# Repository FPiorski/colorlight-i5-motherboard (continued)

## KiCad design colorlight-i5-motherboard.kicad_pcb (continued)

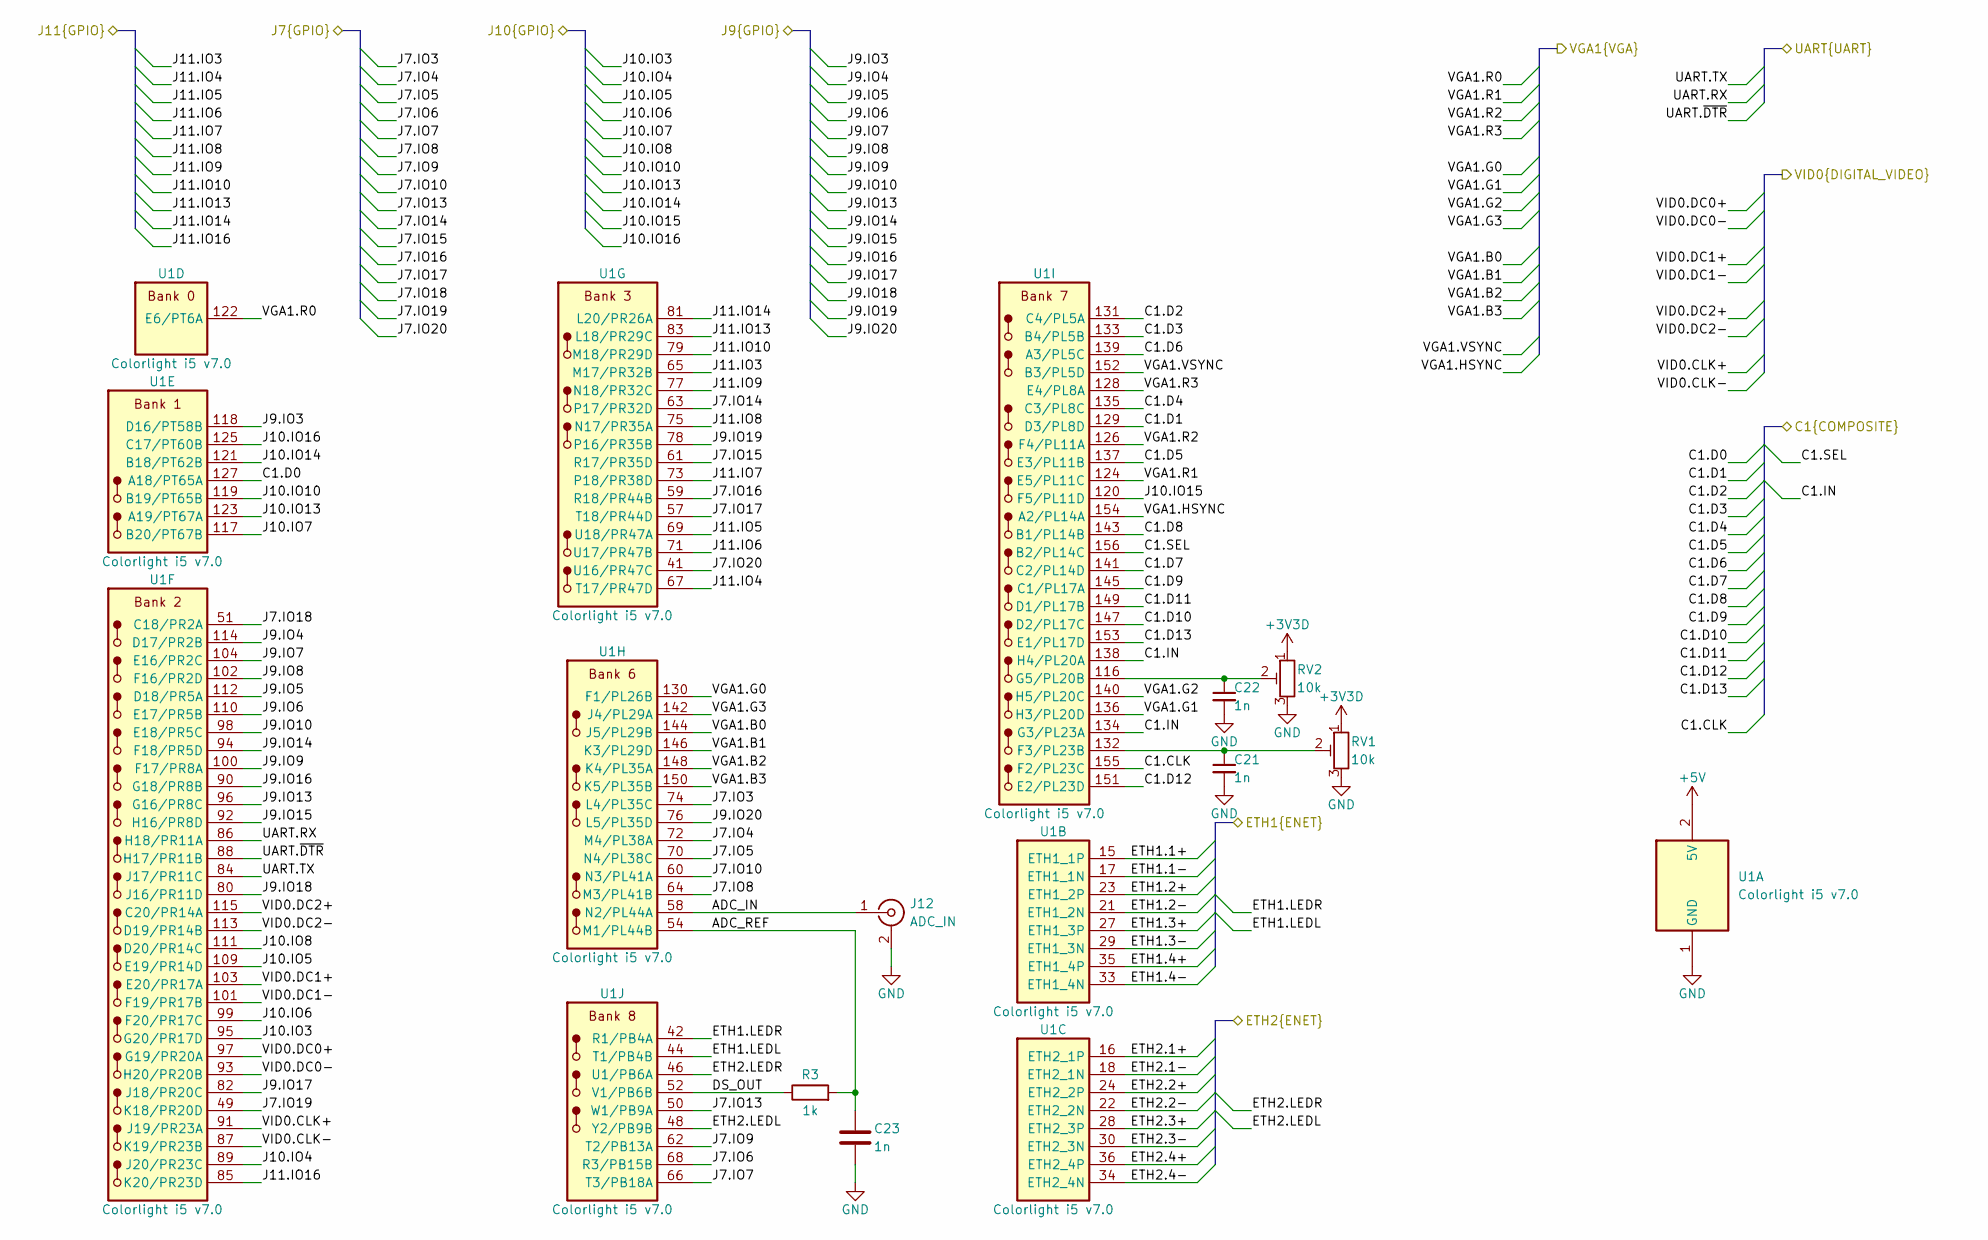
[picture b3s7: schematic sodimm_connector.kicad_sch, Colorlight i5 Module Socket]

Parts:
C21, C22, C23: 1n; C_0402_1005Metric
J12: ADC_IN; U.FL_Hirose_U.FL-R-SMT-1_Vertical; LCSC C5137195
R3: 1k; R_0402_1005Metric
RV1, RV2: 10k; Potentiometer_Bourns_TC33X_Vertical; LCSC C719176
U1: Colorlight i5 v7.0; JST_DM-7D4-H2500_2x100_P0.6mm_Polarized_Socket_Horizontal

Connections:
+3V3D: RV1.1, RV2.1; also elsewhere on the board
+5V: U1.2 (5V), U1.4 (5V), U1.6 (5V), U1.8 (5V), U1.10 (5V), U1.12 (5V); also elsewhere on the board
/Analog Video/C1.CLK: U1.155 (F2/PL23C); also elsewhere on the board
/Analog Video/C1.D0: U1.127 (A18/PT65A); also elsewhere on the board
/Analog Video/C1.D1: U1.129 (D3/PL8D); also elsewhere on the board
/Analog Video/C1.D2: U1.131 (C4/PL5A); also elsewhere on the board
/Analog Video/C1.D3: U1.133 (B4/PL5B); also elsewhere on the board
/Analog Video/C1.D4: U1.135 (C3/PL8C); also elsewhere on the board
/Analog Video/C1.D5: U1.137 (E3/PL11B); also elsewhere on the board
/Analog Video/C1.D6: U1.139 (A3/PL5C); also elsewhere on the board
/Analog Video/C1.D7: U1.141 (C2/PL14D); also elsewhere on the board
/Analog Video/C1.D8: U1.143 (B1/PL14B); also elsewhere on the board
/Analog Video/C1.D9: U1.145 (C1/PL17A); also elsewhere on the board
/Analog Video/C1.D10: U1.147 (D2/PL17C); also elsewhere on the board
/Analog Video/C1.D11: U1.149 (D1/PL17B); also elsewhere on the board
/Analog Video/C1.D12: U1.151 (E2/PL23D); also elsewhere on the board
/Analog Video/C1.D13: U1.153 (E1/PL17D); also elsewhere on the board
/Analog Video/C1.IN: U1.134 (G3/PL23A), U1.138 (H4/PL20A); also elsewhere on the board
/Analog Video/C1.SEL: U1.156 (B2/PL14C); also elsewhere on the board
/Analog Video/VGA1.B0: U1.144 (J5/PL29B); also elsewhere on the board
/Analog Video/VGA1.B1: U1.146 (K3/PL29D); also elsewhere on the board
/Analog Video/VGA1.B2: U1.148 (K4/PL35A); also elsewhere on the board
/Analog Video/VGA1.B3: U1.150 (K5/PL35B); also elsewhere on the board
/Analog Video/VGA1.G0: U1.130 (F1/PL26B); also elsewhere on the board
/Analog Video/VGA1.G1: U1.136 (H3/PL20D); also elsewhere on the board
/Analog Video/VGA1.G2: U1.140 (H5/PL20C); also elsewhere on the board
/Analog Video/VGA1.G3: U1.142 (J4/PL29A); also elsewhere on the board
/Analog Video/VGA1.HSYNC: U1.154 (A2/PL14A); also elsewhere on the board
/Analog Video/VGA1.R0: U1.122 (E6/PT6A); also elsewhere on the board
/Analog Video/VGA1.R1: U1.124 (E5/PL11C); also elsewhere on the board
/Analog Video/VGA1.R2: U1.126 (F4/PL11A); also elsewhere on the board
/Analog Video/VGA1.R3: U1.128 (E4/PL8A); also elsewhere on the board
/Analog Video/VGA1.VSYNC: U1.152 (B3/PL5D); also elsewhere on the board
/Digital Video/VID0.CLK+: U1.91 (J19/PR23A); also elsewhere on the board
/Digital Video/VID0.CLK-: U1.87 (K19/PR23B); also elsewhere on the board
/Digital Video/VID0.DC0+: U1.97 (G19/PR20A); also elsewhere on the board
/Digital Video/VID0.DC0-: U1.93 (H20/PR20B); also elsewhere on the board
/Digital Video/VID0.DC1+: U1.103 (E20/PR17A); also elsewhere on the board
/Digital Video/VID0.DC1-: U1.101 (F19/PR17B); also elsewhere on the board
/Digital Video/VID0.DC2+: U1.115 (C20/PR14A); also elsewhere on the board
/Digital Video/VID0.DC2-: U1.113 (D19/PR14B); also elsewhere on the board
/Ethernet/ETH1.1+: U1.15 (ETH1_1P); also elsewhere on the board
/Ethernet/ETH1.1-: U1.17 (ETH1_1N); also elsewhere on the board
/Ethernet/ETH1.2+: U1.23 (ETH1_2P); also elsewhere on the board
/Ethernet/ETH1.2-: U1.21 (ETH1_2N); also elsewhere on the board
/Ethernet/ETH1.3+: U1.27 (ETH1_3P); also elsewhere on the board
/Ethernet/ETH1.3-: U1.29 (ETH1_3N); also elsewhere on the board
/Ethernet/ETH1.4+: U1.35 (ETH1_4P); also elsewhere on the board
/Ethernet/ETH1.4-: U1.33 (ETH1_4N); also elsewhere on the board
/Ethernet/ETH1.LEDL: U1.44 (T1/PB4B); also elsewhere on the board
/Ethernet/ETH1.LEDR: U1.42 (R1/PB4A); also elsewhere on the board
/Ethernet/ETH2.1+: U1.16 (ETH2_1P); also elsewhere on the board
/Ethernet/ETH2.1-: U1.18 (ETH2_1N); also elsewhere on the board
/Ethernet/ETH2.2+: U1.24 (ETH2_2P); also elsewhere on the board
/Ethernet/ETH2.2-: U1.22 (ETH2_2N); also elsewhere on the board
/Ethernet/ETH2.3+: U1.28 (ETH2_3P); also elsewhere on the board
/Ethernet/ETH2.3-: U1.30 (ETH2_3N); also elsewhere on the board
/Ethernet/ETH2.4+: U1.36 (ETH2_4P); also elsewhere on the board
/Ethernet/ETH2.4-: U1.34 (ETH2_4N); also elsewhere on the board
/Ethernet/ETH2.LEDL: U1.48 (Y2/PB9B); also elsewhere on the board
/Ethernet/ETH2.LEDR: U1.46 (U1/PB6A); also elsewhere on the board
/GPIO/J7.IO3: U1.74 (L4/PL35C); also elsewhere on the board
/GPIO/J7.IO4: U1.72 (M4/PL38A); also elsewhere on the board
/GPIO/J7.IO5: U1.70 (N4/PL38C); also elsewhere on the board
/GPIO/J7.IO6: U1.68 (R3/PB15B); also elsewhere on the board
/GPIO/J7.IO7: U1.66 (T3/PB18A); also elsewhere on the board
/GPIO/J7.IO8: U1.64 (M3/PL41B); also elsewhere on the board
/GPIO/J7.IO9: U1.62 (T2/PB13A); also elsewhere on the board
/GPIO/J7.IO10: U1.60 (N3/PL41A); also elsewhere on the board
/GPIO/J7.IO13: U1.50 (W1/PB9A); also elsewhere on the board
/GPIO/J7.IO14: U1.63 (P17/PR32D); also elsewhere on the board
/GPIO/J7.IO15: U1.61 (R17/PR35D); also elsewhere on the board
/GPIO/J7.IO16: U1.59 (R18/PR44B); also elsewhere on the board
/GPIO/J7.IO17: U1.57 (T18/PR44D); also elsewhere on the board
/GPIO/J7.IO18: U1.51 (C18/PR2A); also elsewhere on the board
/GPIO/J7.IO19: U1.49 (K18/PR20D); also elsewhere on the board
/GPIO/J7.IO20: U1.41 (U16/PR47C); also elsewhere on the board
/GPIO/J9.IO3: U1.118 (D16/PT58B); also elsewhere on the board
/GPIO/J9.IO4: U1.114 (D17/PR2B); also elsewhere on the board
/GPIO/J9.IO5: U1.112 (D18/PR5A); also elsewhere on the board
/GPIO/J9.IO6: U1.110 (E17/PR5B); also elsewhere on the board
/GPIO/J9.IO7: U1.104 (E16/PR2C); also elsewhere on the board
/GPIO/J9.IO8: U1.102 (F16/PR2D); also elsewhere on the board
/GPIO/J9.IO9: U1.100 (F17/PR8A); also elsewhere on the board
/GPIO/J9.IO10: U1.98 (E18/PR5C); also elsewhere on the board
/GPIO/J9.IO13: U1.96 (G16/PR8C); also elsewhere on the board
/GPIO/J9.IO14: U1.94 (F18/PR5D); also elsewhere on the board
/GPIO/J9.IO15: U1.92 (H16/PR8D); also elsewhere on the board
/GPIO/J9.IO16: U1.90 (G18/PR8B); also elsewhere on the board
/GPIO/J9.IO17: U1.82 (J18/PR20C); also elsewhere on the board
/GPIO/J9.IO18: U1.80 (J16/PR11D); also elsewhere on the board
/GPIO/J9.IO19: U1.78 (P16/PR35B); also elsewhere on the board
/GPIO/J9.IO20: U1.76 (L5/PL35D); also elsewhere on the board
/GPIO/J10.IO3: U1.95 (G20/PR17D); also elsewhere on the board
/GPIO/J10.IO4: U1.89 (J20/PR23C); also elsewhere on the board
/GPIO/J10.IO5: U1.109 (E19/PR14D); also elsewhere on the board
/GPIO/J10.IO6: U1.99 (F20/PR17C); also elsewhere on the board
/GPIO/J10.IO7: U1.117 (B20/PT67B); also elsewhere on the board
/GPIO/J10.IO8: U1.111 (D20/PR14C); also elsewhere on the board
/GPIO/J10.IO10: U1.119 (B19/PT65B); also elsewhere on the board
/GPIO/J10.IO13: U1.123 (A19/PT67A); also elsewhere on the board
/GPIO/J10.IO14: U1.121 (B18/PT62B); also elsewhere on the board
/GPIO/J10.IO15: U1.120 (F5/PL11D); also elsewhere on the board
/GPIO/J10.IO16: U1.125 (C17/PT60B); also elsewhere on the board
/GPIO/J11.IO3: U1.65 (M17/PR32B); also elsewhere on the board
/GPIO/J11.IO4: U1.67 (T17/PR47D); also elsewhere on the board
/GPIO/J11.IO5: U1.69 (U18/PR47A); also elsewhere on the board
/GPIO/J11.IO6: U1.71 (U17/PR47B); also elsewhere on the board
/GPIO/J11.IO7: U1.73 (P18/PR38D); also elsewhere on the board
/GPIO/J11.IO8: U1.75 (N17/PR35A); also elsewhere on the board
/GPIO/J11.IO9: U1.77 (N18/PR32C); also elsewhere on the board
/GPIO/J11.IO10: U1.79 (M18/PR29D); also elsewhere on the board
/GPIO/J11.IO13: U1.83 (L18/PR29C); also elsewhere on the board
/GPIO/J11.IO14: U1.81 (L20/PR26A); also elsewhere on the board
/GPIO/J11.IO16: U1.85 (K20/PR23D); also elsewhere on the board
/SODIMM Connector/ADC_IN: J12.1 (In), U1.58 (N2/PL44A)
/SODIMM Connector/ADC_REF: C23.1, R3.2, U1.54 (M1/PL44B)
/SODIMM Connector/DS_OUT: R3.1, U1.52 (V1/PB6B)
/SODIMM Connector/UART.RX: U1.86 (H18/PR11A); also elsewhere on the board
/SODIMM Connector/UART.TX: U1.84 (J17/PR11C); also elsewhere on the board
/SODIMM Connector/UART.~DTR: U1.88 (H17/PR11B); also elsewhere on the board
GND: C21.2, C22.2, C23.2, J12.2 (Ext), RV1.3, RV2.3, U1.1 (GND), U1.3 (GND), U1.5 (GND), U1.7 (GND), U1.9 (GND), U1.11 (GND), U1.39 (GND), U1.40 (GND), U1.55 (GND), U1.56 (GND), U1.105 (GND), U1.106 (GND), U1.107 (GND), U1.108 (GND), U1.157 (GND), U1.158 (GND), U1.199 (GND), U1.200 (GND); also elsewhere on the board
unnamed: C21.1, RV1.2, U1.132 (F3/PL23B)
unnamed: C22.1, RV2.2, U1.116 (G5/PL20B)

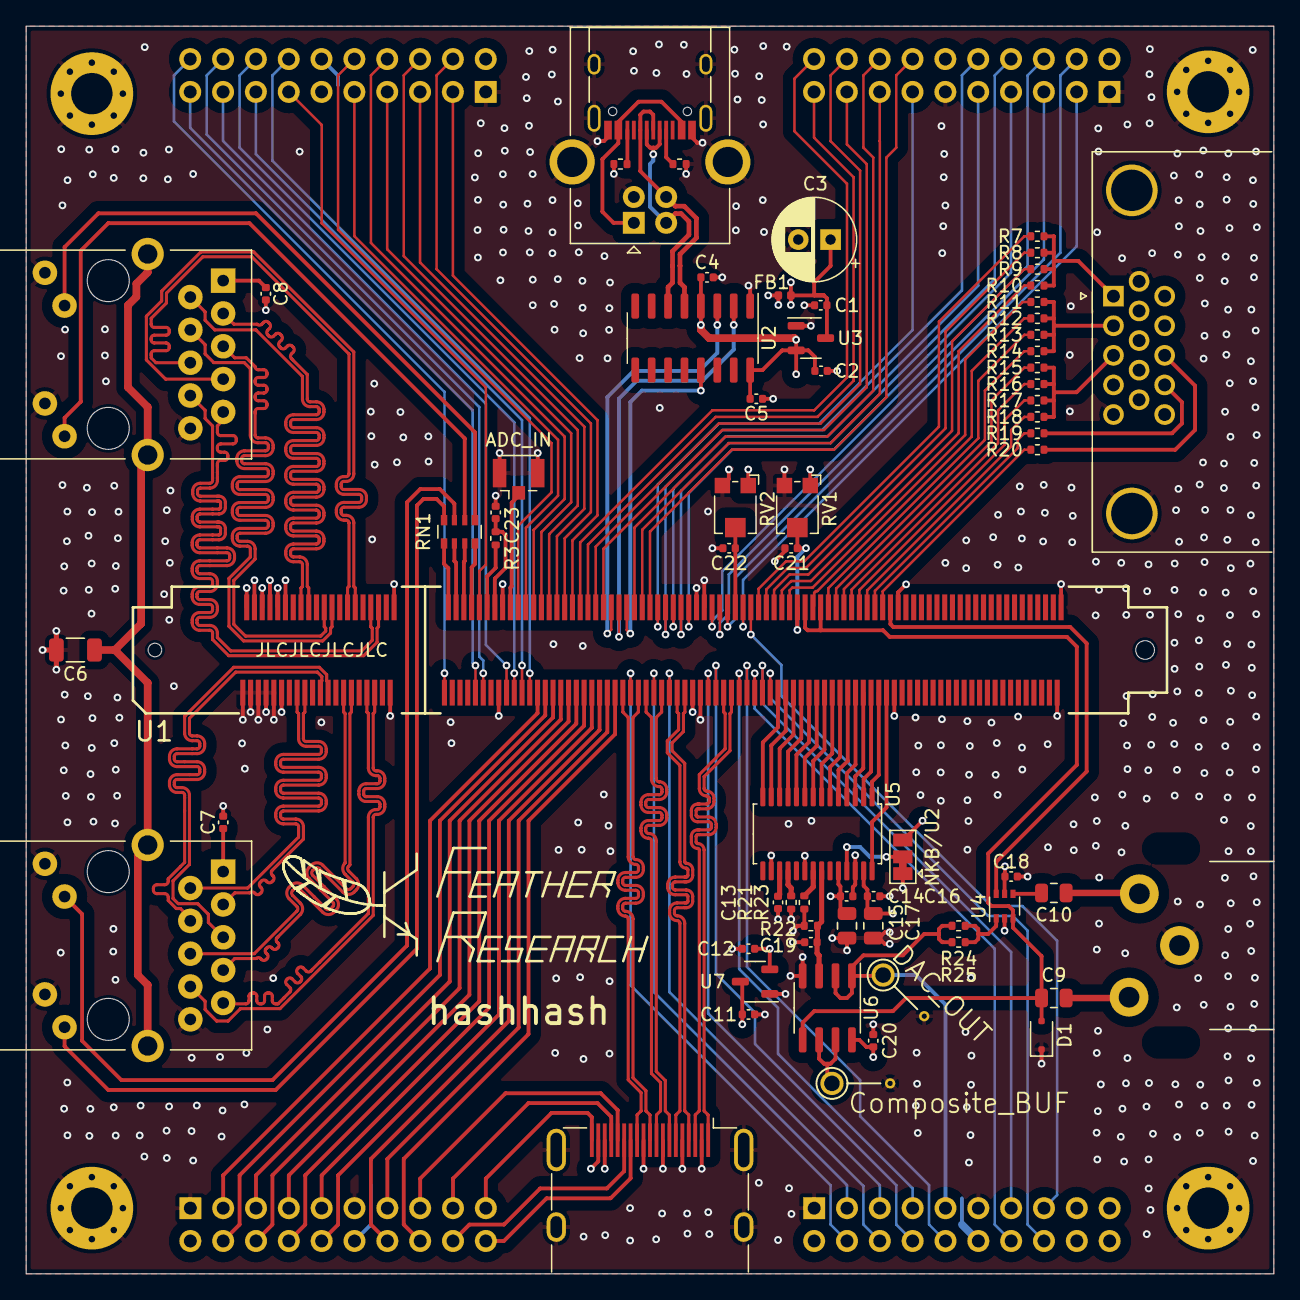
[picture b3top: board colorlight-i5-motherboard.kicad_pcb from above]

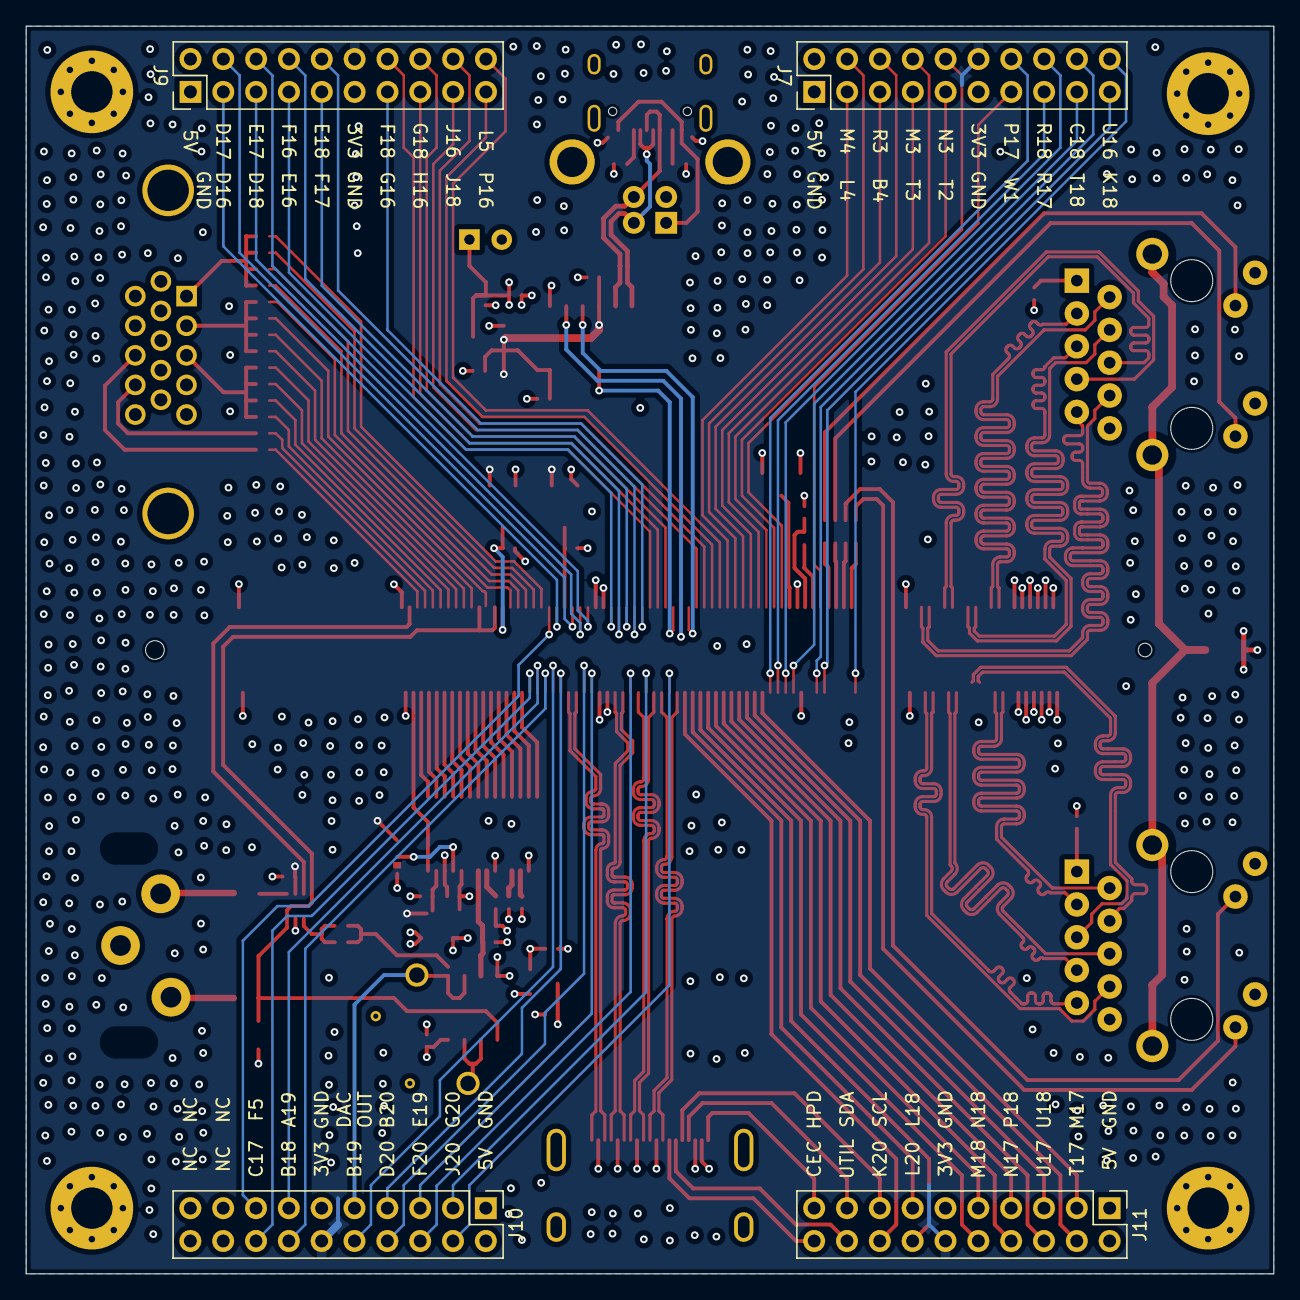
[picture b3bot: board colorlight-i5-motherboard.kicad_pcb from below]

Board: 4 copper layers, 96.5 x 96.5 mm, 76 parts (4 on the bottom side), 158 nets.

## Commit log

2024-05-12 Initial PCB commit
2024-05-13 Improve Ethernet skew matching
2024-05-13 Add gen_out.sh
2024-05-15 Add LED and Button expansion boards
